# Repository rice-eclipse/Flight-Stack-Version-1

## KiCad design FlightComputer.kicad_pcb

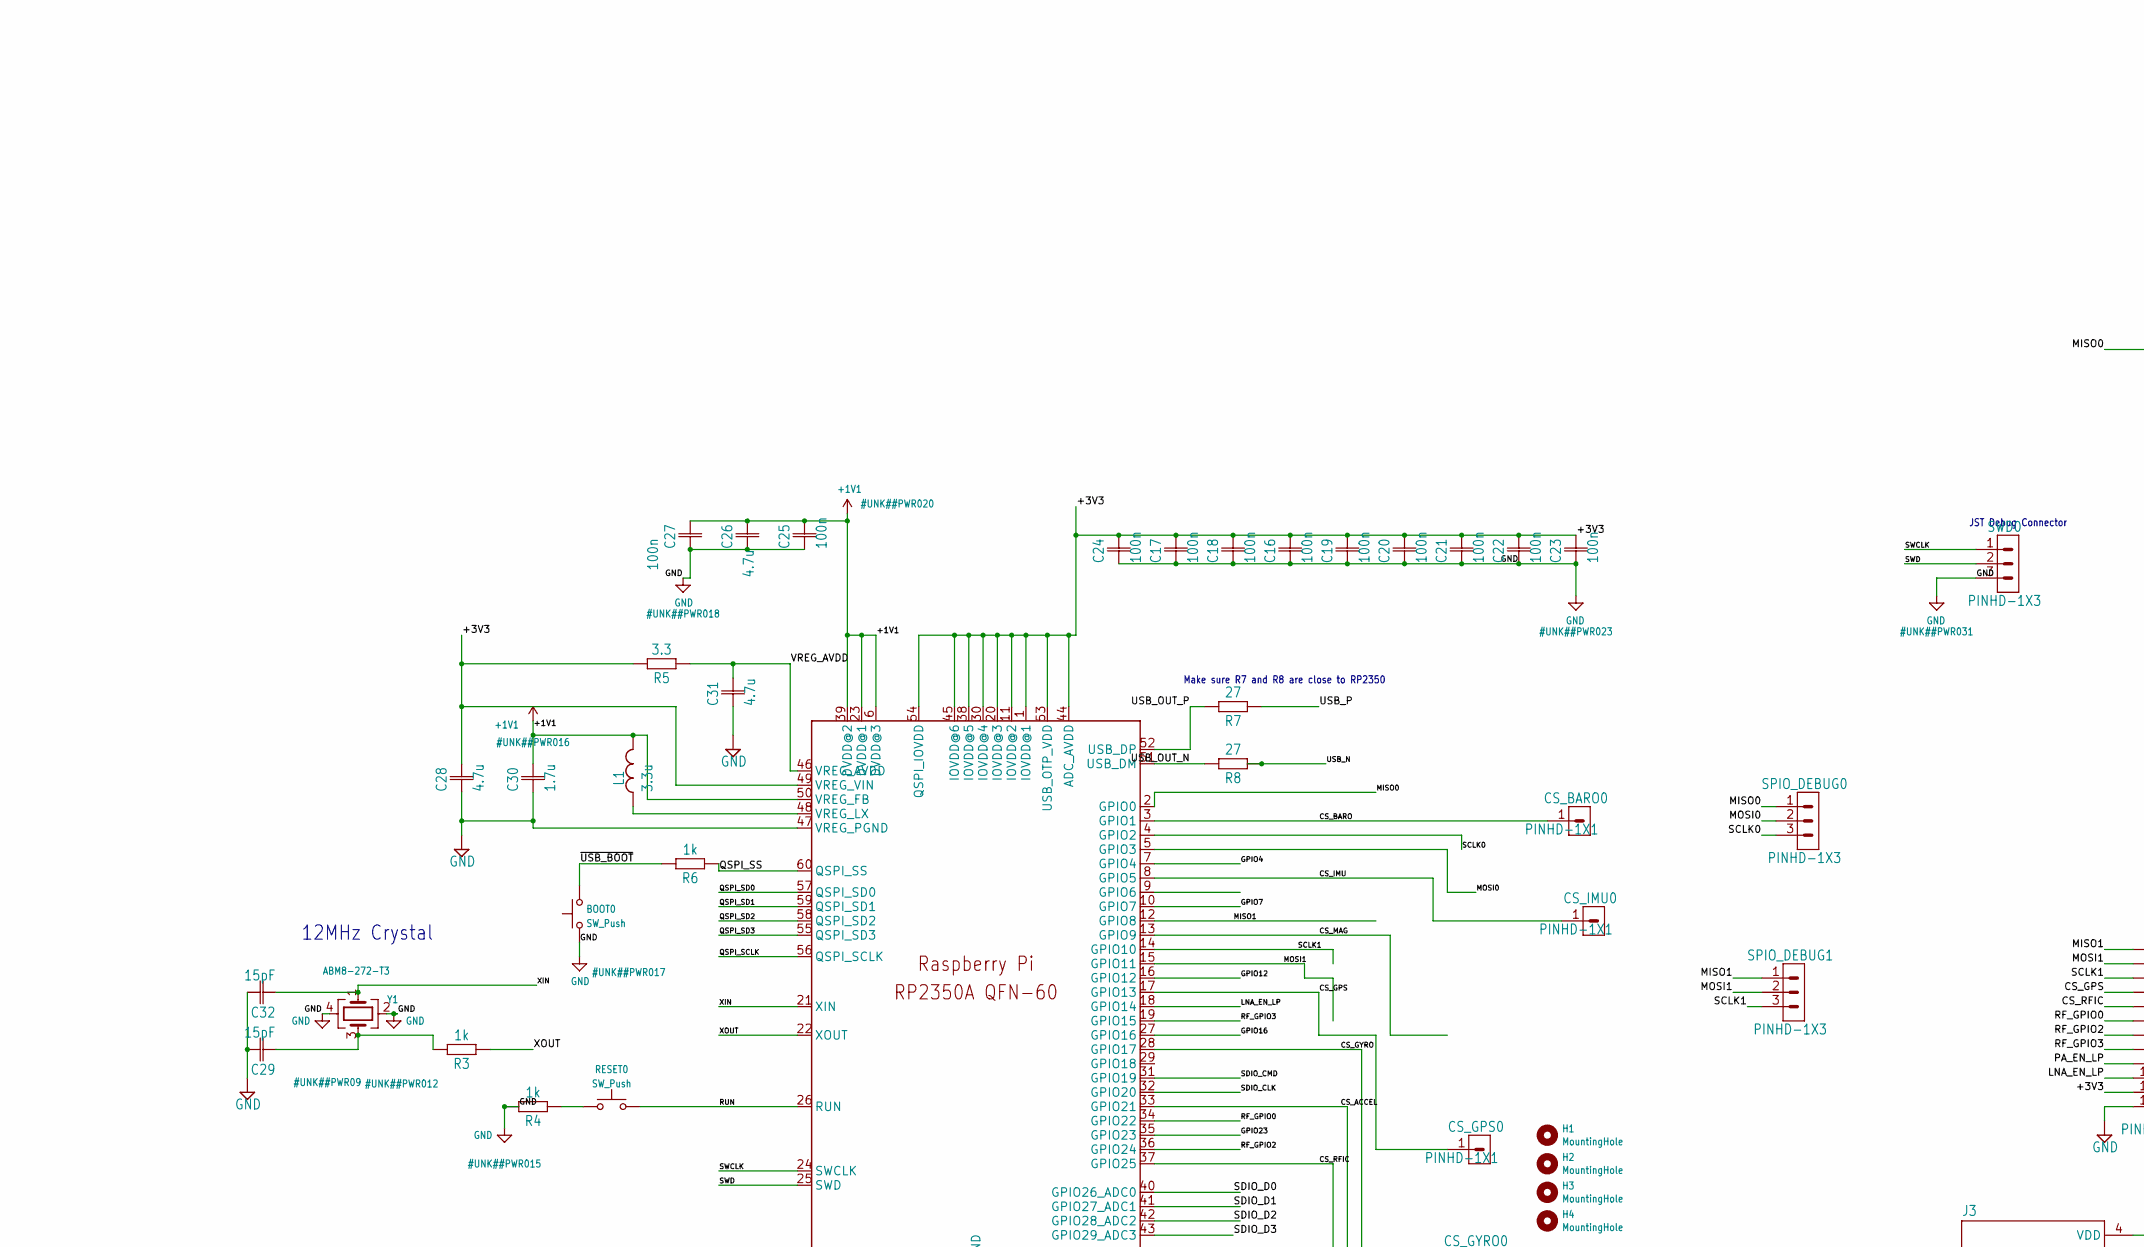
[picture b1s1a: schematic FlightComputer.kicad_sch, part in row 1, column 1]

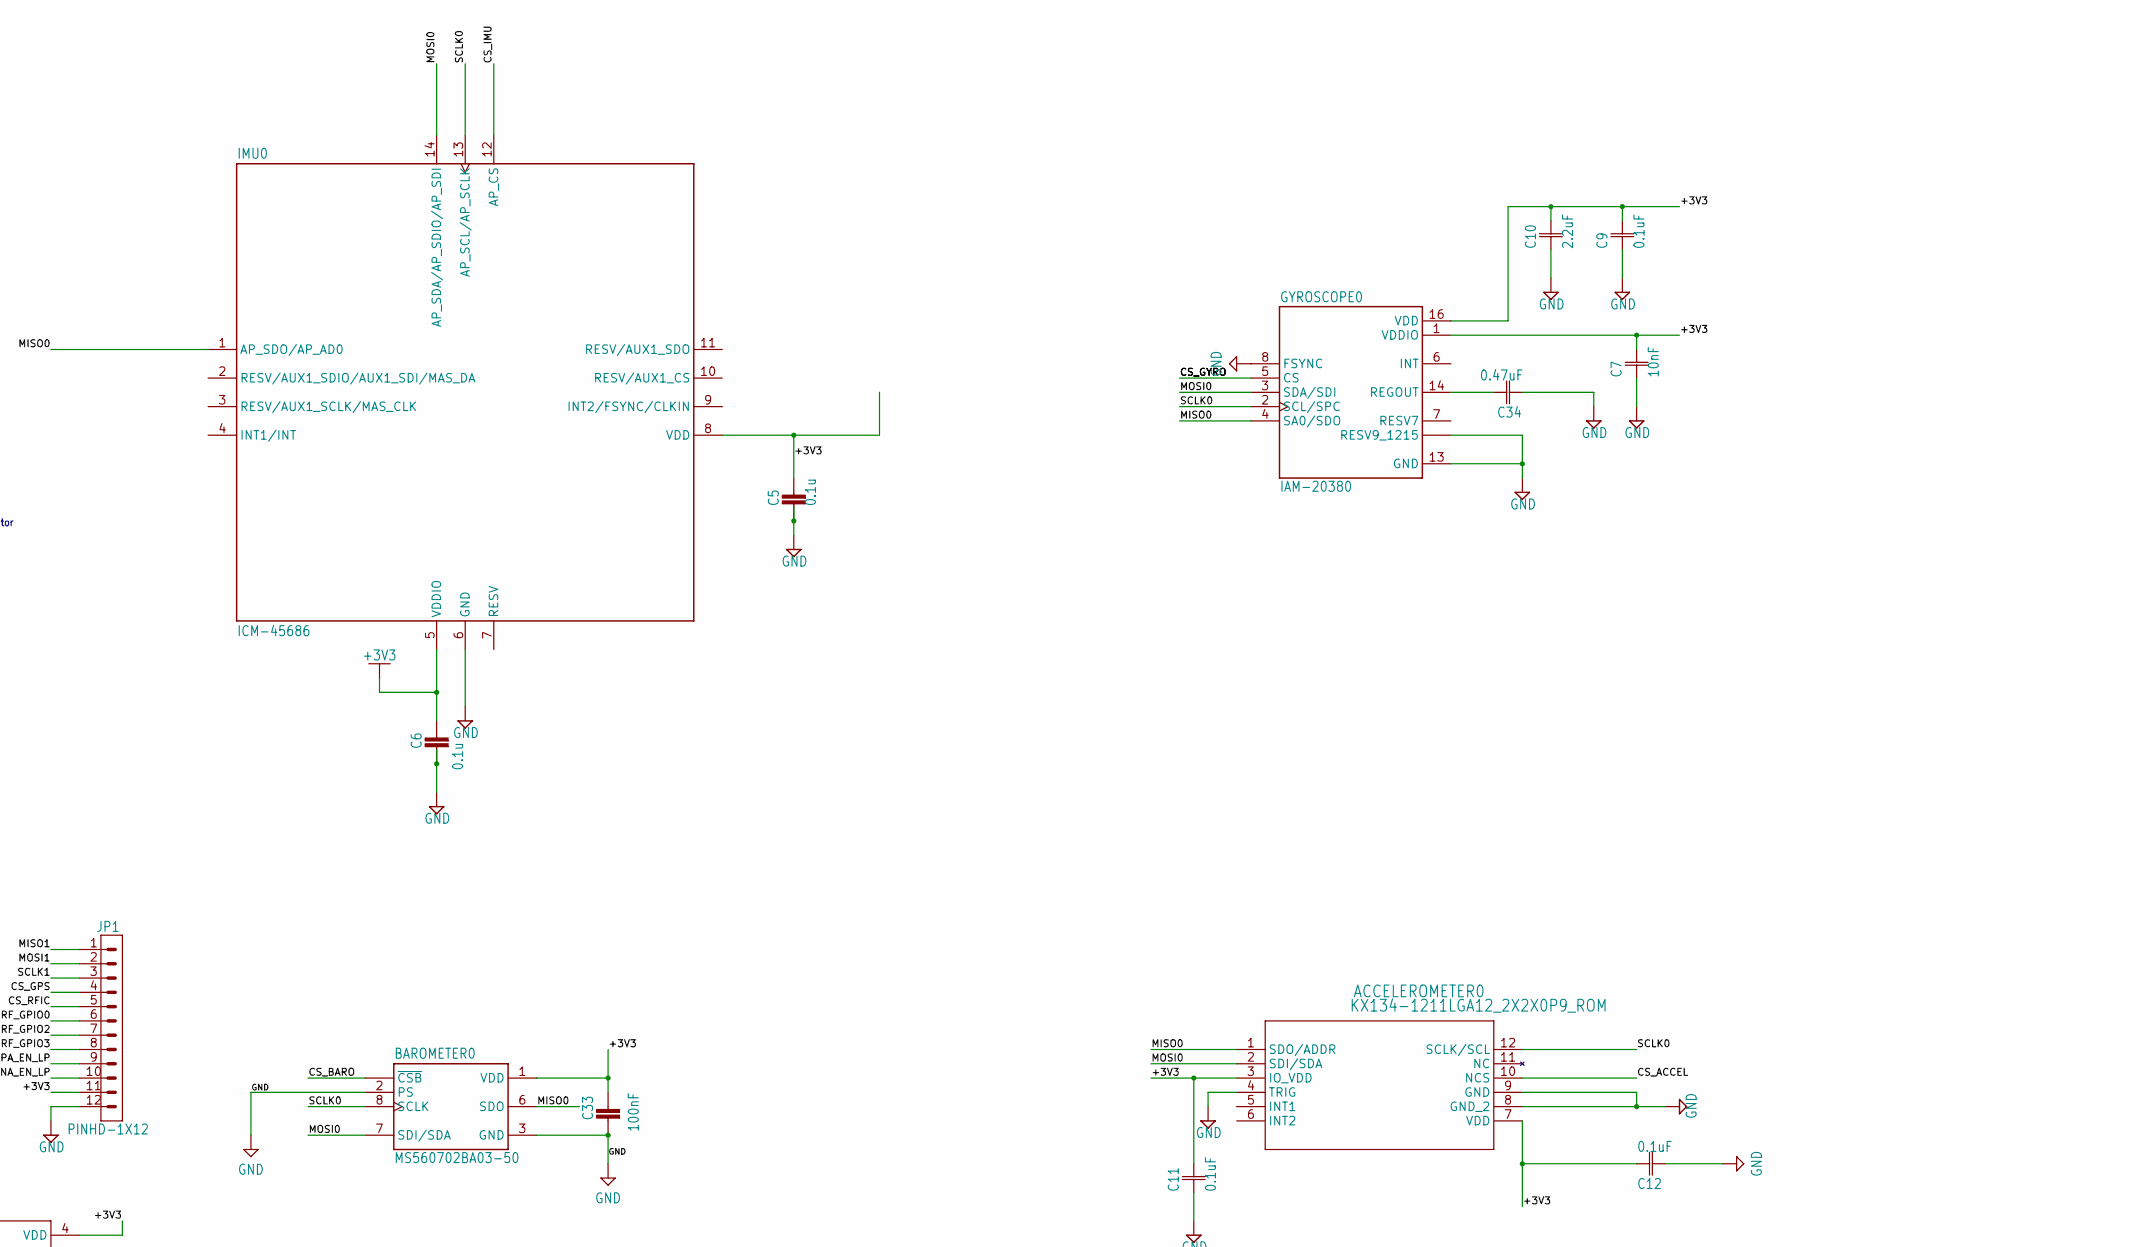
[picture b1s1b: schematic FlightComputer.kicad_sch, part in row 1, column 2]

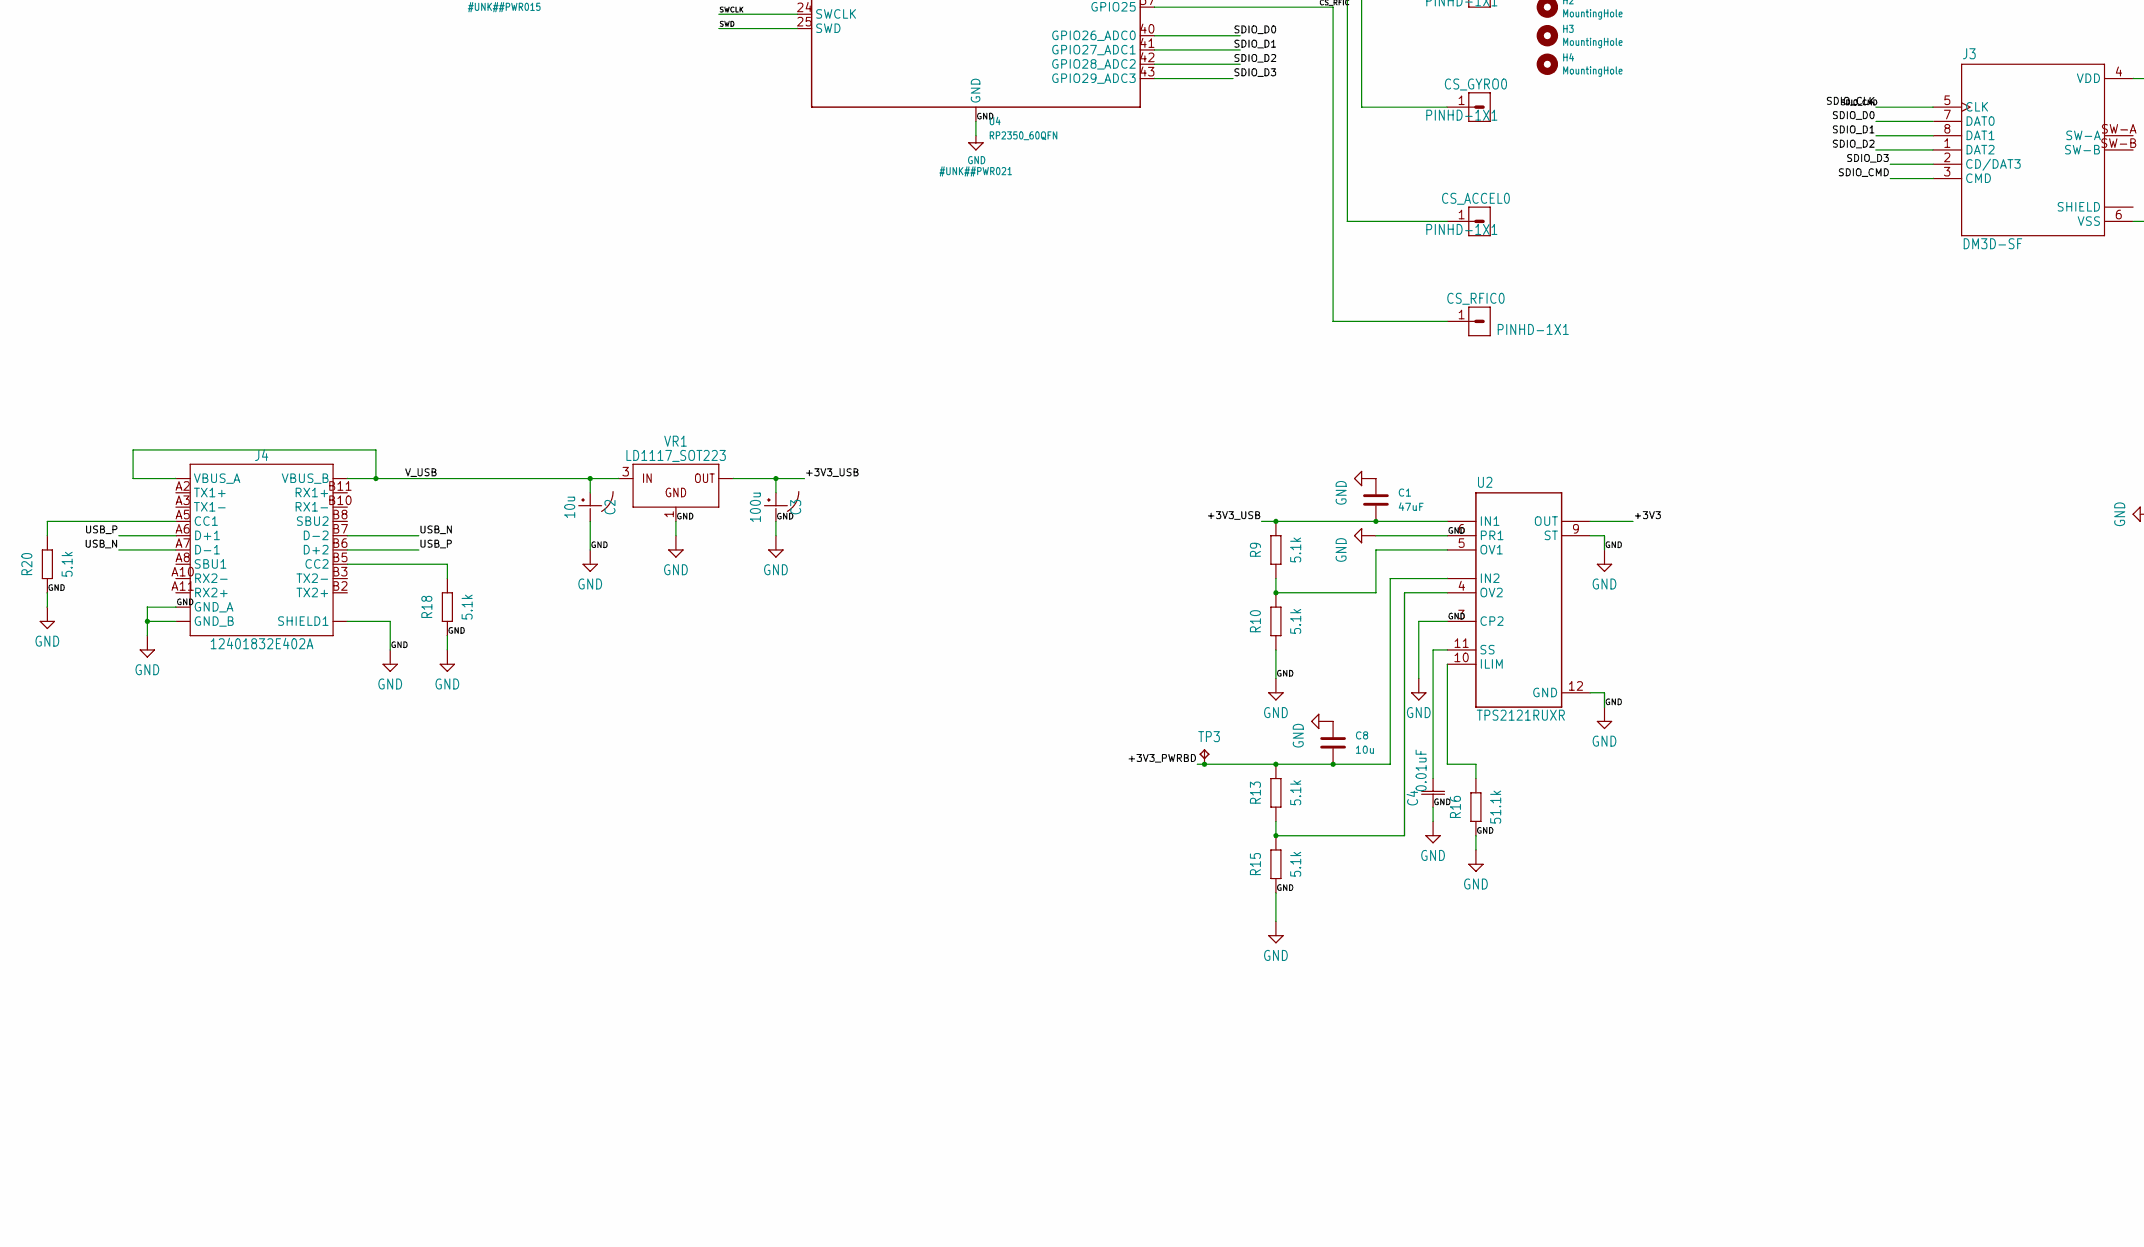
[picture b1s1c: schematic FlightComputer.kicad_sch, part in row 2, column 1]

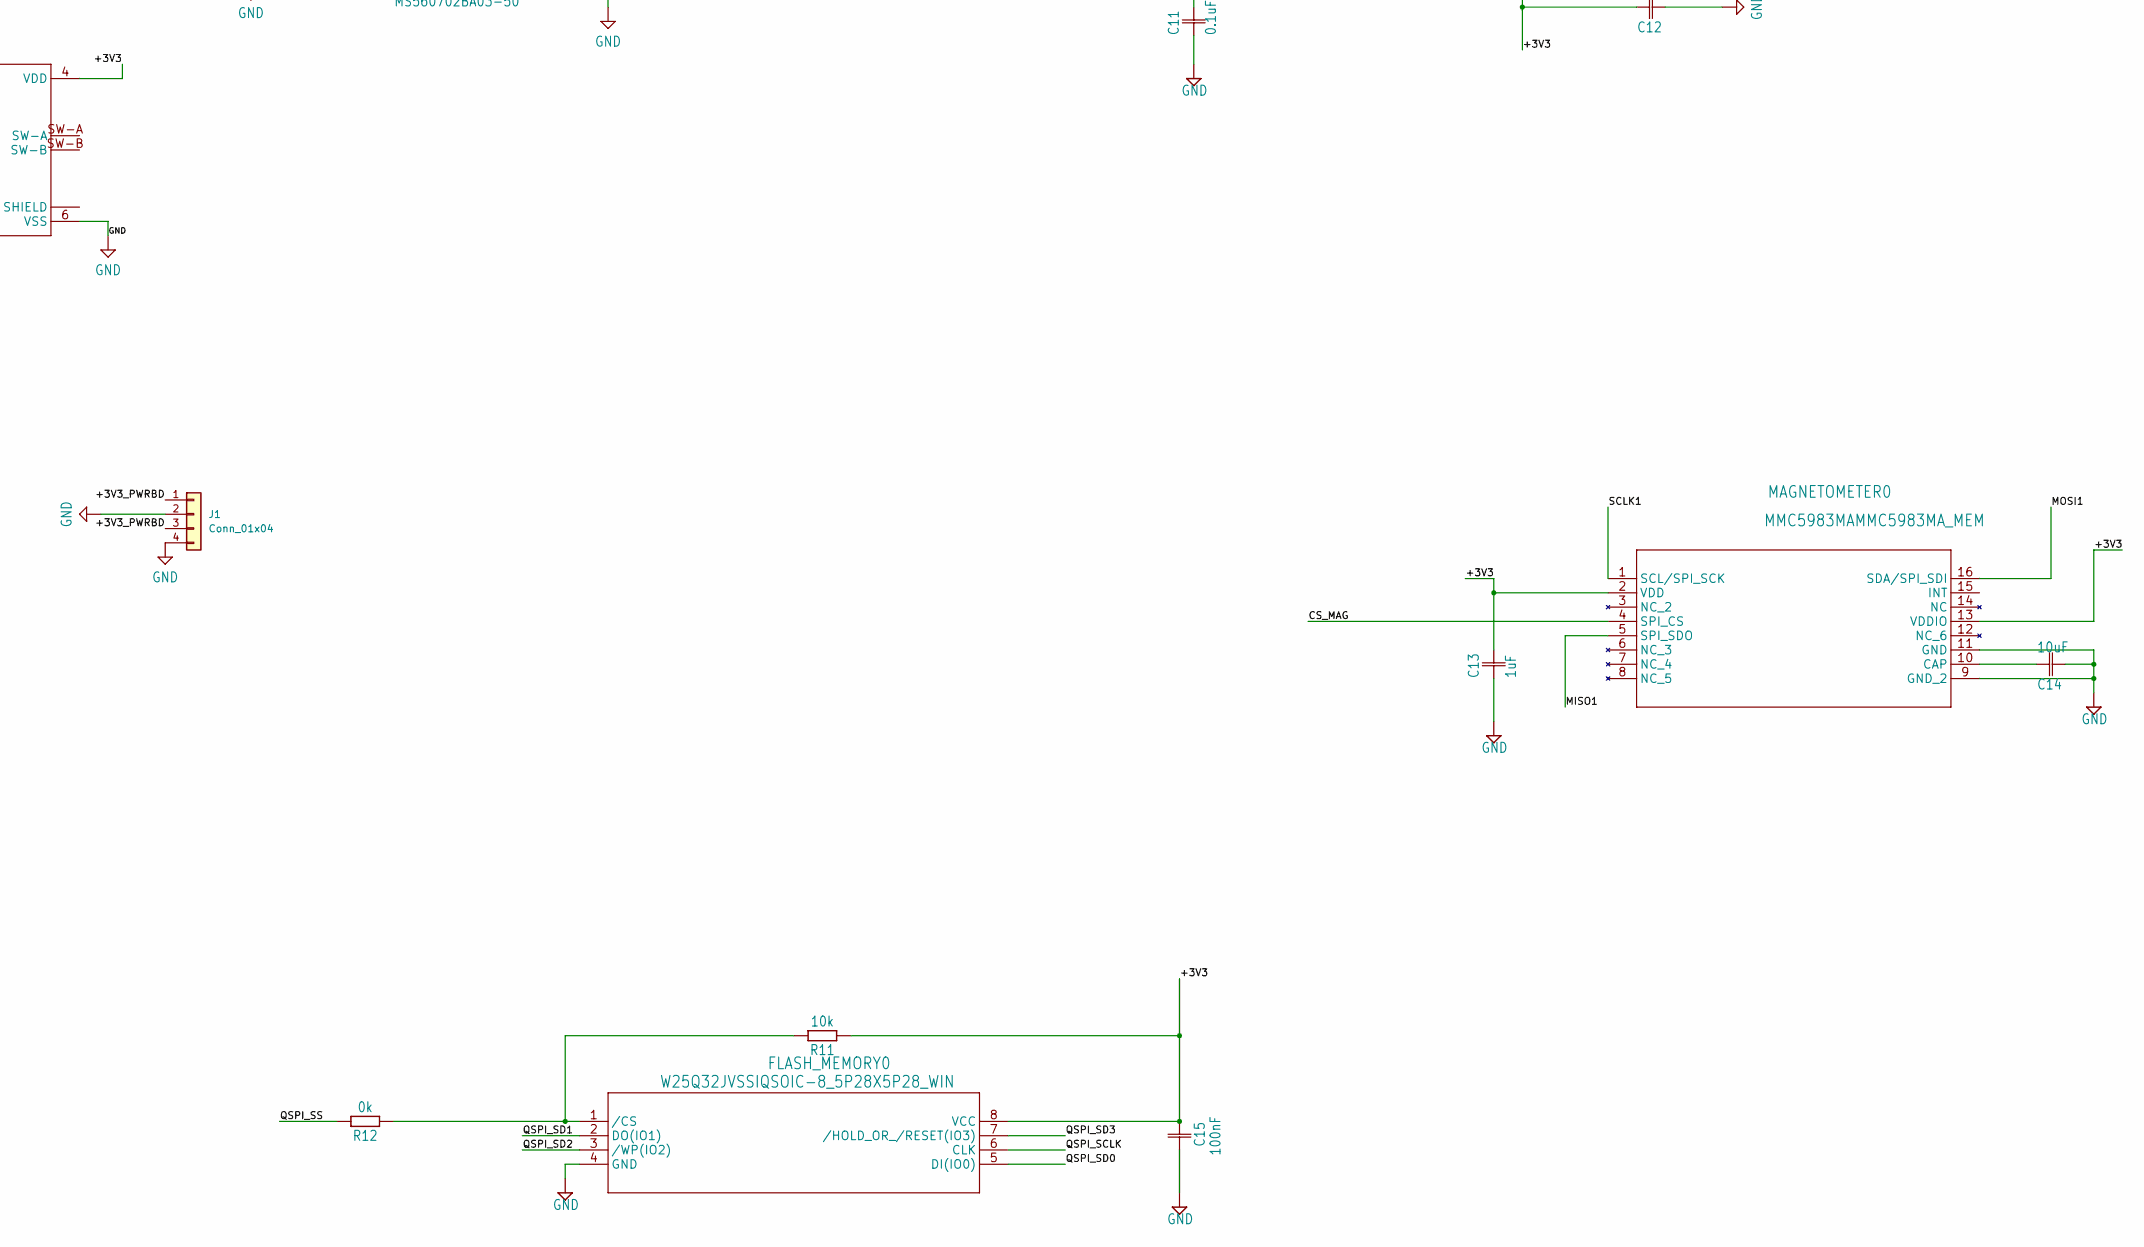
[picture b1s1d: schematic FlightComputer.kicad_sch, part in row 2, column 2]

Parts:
ACCELEROMETER0: KX134-1211LGA12_2X2X0P9_ROM; LGA12_2X2X0P9_ROM
BAROMETER0: MS560702BA03-50; SON125P300X500X100-8N
BOOT0: SW_Push; SW_Push_1P1T_NO_Vertical_Wuerth_434133025816
C1: 47uF
C2: 10u; CAPMP3216X180N
C3: 100u; CAPMP3216X180N
C4: 0.01uF; CAPC1005X60
C5, C6: 0.1u; CAPC2012X110
C7: 10nF; CAPC1608X85
C8: 10u
C9, C11, C12: 0.1uF; CAPC1608X85
C10: 2.2uF; CAPC1608X85
C13: 1uF; CAPC1608X85
C14: 10uF; CAPC1608X85
C15: 100nF; CAPC1608X85
C16, C17, C18, C20, C21, C22, C23, C24, C25, C27: 100n; CAPC1608X85
C19: 100n; CAPC1005X60
C26, C28, C31: 4.7u; CAPC1608X85
C29, C32: 15pF; CAPC1005X60
C30: 1.7u; CAPC1608X85
C33: 100nF; CAPC2012X110
C34: 0.47uF; CAPC1608X85
CS_ACCEL0: PINHD-1X1; 1X01
CS_BARO0: PINHD-1X1; 1X01
CS_GPS0: PINHD-1X1; 1X01
CS_GYRO0: PINHD-1X1; 1X01
CS_IMU0: PINHD-1X1; 1X01
CS_RFIC0: PINHD-1X1; 1X01
FLASH_MEMORY0: W25Q32JVSSIQSOIC-8_5P28X5P28_WIN; SOIC-8_5P28X5P28_WIN
GYROSCOPE0: IAM-20380; PQFN50P300X300X80-16N
H1, H2, H3, H4: MountingHole; MountingHole_2.7mm_M2.5
IMU0: ICM-45686; IC_ICM-45686
J1: Conn_01x04; JST_GH_BM04B-GHS-TBT_1x04-1MP_P1.25mm_Vertical
J3: DM3D-SF; HRS_DM3D-SF
J4: 12401832E402A
JP1: PINHD-1X12; 1X12
L1: 3.3u; INDC2009X120
MAGNETOMETER0: MMC5983MAMMC5983MA_MEM; MMC5983MA_MEM
R3: 1k; RESC1005X40
R4, R6: 1k; RESC1608X60
R5: 3.3; RESC1608X60
R7, R8: 27; RESC1608X60
R9, R10, R13, R15, R18, R20: 5.1k; RESC1005X40
R11: 10k; RESC2012X65
R12: 0k; RESC2012X65
R16: 51.1k; RESC1005X40
RESET0: SW_Push; SW_Push_1P1T_NO_Vertical_Wuerth_434133025816
SPIO_DEBUG0, SPIO_DEBUG1: PINHD-1X3; 1X03
SWD0: PINHD-1X3; 1X03
TP3: TPB1,27; B1,27
U2: TPS2121RUXR; IC_TPS2121RUXR
U4: RP2350_60QFN; RP2350-QFN-60-1EP_7x7_P0.4mm_EP3.4x3.4mm_ThermalVias
VR1: LD1117_SOT223; SOT230P700X170-4
Y1: ABM8-272-T3; Crystal_SMD_3225-4Pin_3.2x2.5mm

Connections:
+1V1: C25.2, C26.2, C27.2, C30.2, L1.2, U4.6 (DVDD@3), U4.23 (DVDD@1), U4.39 (DVDD@2), U4.50 (VREG_FB)
+3V3: ACCELEROMETER0.3 (IO_VDD), ACCELEROMETER0.7 (VDD), BAROMETER0.1 (VDD), C5.1, C6.1, C7.2, C9.2, C10.2, C11.2, C12.1, C13.2, C15.1, C16.2, C17.2, C18.2, C19.2, C20.2, C21.2, C22.2, C23.2, C24.2, C28.2, C33.1, FLASH_MEMORY0.8 (VCC), GYROSCOPE0.1 (VDDIO), GYROSCOPE0.16 (VDD), IMU0.5 (VDDIO), IMU0.8 (VDD), J3.4 (VDD), JP1.11, MAGNETOMETER0.2 (VDD), MAGNETOMETER0.13 (VDDIO), R5.2, R11.1, U2.1 (OUT), U2.1_1 (OUT), U2.8 (OUT), U2.8_1 (OUT), U4.1 (IOVDD@1), U4.11 (IOVDD@2), U4.20 (IOVDD@3), U4.30 (IOVDD@4), U4.38 (IOVDD@5), U4.44 (ADC_AVDD), U4.45 (IOVDD@6), U4.49 (VREG_VIN), U4.53 (USB_OTP_VDD), U4.54 (QSPI_IOVDD)
/+3V3_PWRBD: C8.2, J1.1, J1.3, R13.2, TP3.TP (TP_TP), U2.2 (IN2), U2.2_1 (IN2)
/+3V3_USB: C1.2, C3.1 (+), R9.2, U2.7 (IN1), U2.7_1 (IN1), VR1.2 (VO), VR1.4 (VO)
/CS_ACCEL: ACCELEROMETER0.10 (NCS), CS_ACCEL0.1 (1_1), U4.33 (GPIO21)
/CS_BARO: BAROMETER0.4 (~CSB), BAROMETER0.5 (~CSB), CS_BARO0.1 (1_1), U4.3 (GPIO1)
/CS_GPS: CS_GPS0.1 (1_1), JP1.4, U4.17 (GPIO13)
/CS_GYRO: CS_GYRO0.1 (1_1), GYROSCOPE0.5 (CS), U4.28 (GPIO17)
/CS_IMU: CS_IMU0.1 (1_1), IMU0.12 (AP_CS), U4.8 (GPIO5)
/CS_MAG: MAGNETOMETER0.4 (SPI_CS), U4.13 (GPIO9)
/CS_RFIC: CS_RFIC0.1 (1_1), JP1.5, U4.37 (GPIO25)
/GPIO4: U4.7 (GPIO4)
/GPIO7: U4.10 (GPIO7)
/GPIO12: U4.16 (GPIO12)
/GPIO16: U4.27 (GPIO16)
/GPIO23: U4.35 (GPIO23)
/LNA_EN_LP: JP1.10, U4.18 (GPIO14)
/MISO0: ACCELEROMETER0.1 (SDO/ADDR), BAROMETER0.6 (SDO), GYROSCOPE0.4 (SA0/SDO), IMU0.1 (AP_SDO/AP_AD0), SPIO_DEBUG0.1, U4.2 (GPIO0)
/MISO1: JP1.1, MAGNETOMETER0.5 (SPI_SDO), SPIO_DEBUG1.1, U4.12 (GPIO8)
/MOSI0: ACCELEROMETER0.2 (SDI/SDA), BAROMETER0.7 (SDI/SDA), GYROSCOPE0.3 (SDA/SDI), IMU0.14 (AP_SDA/AP_SDIO/AP_SDI), SPIO_DEBUG0.2, U4.5 (GPIO3)
/MOSI1: JP1.2, MAGNETOMETER0.16 (SDA/SPI_SDI), SPIO_DEBUG1.2, U4.15 (GPIO11)
/PA_EN_LP: JP1.9
/QSPI_SCLK: FLASH_MEMORY0.6 (CLK), U4.56 (QSPI_SCLK)
/QSPI_SD0: FLASH_MEMORY0.5 (DI(IO0)), U4.57 (QSPI_SD0)
/QSPI_SD1: FLASH_MEMORY0.2 (DO(IO1)), U4.59 (QSPI_SD1)
/QSPI_SD2: FLASH_MEMORY0.3 (/WP(IO2)), U4.58 (QSPI_SD2)
/QSPI_SD3: FLASH_MEMORY0.7 (/HOLD_OR_/RESET(IO3)), U4.55 (QSPI_SD3)
/QSPI_SS: R6.1, R12.2, U4.60 (QSPI_SS)
/RF_GPIO0: JP1.6, U4.34 (GPIO22)
/RF_GPIO2: JP1.7, U4.36 (GPIO24)
/RF_GPIO3: JP1.8, U4.19 (GPIO15)
/RUN: RESET0.2_1 (2), RESET0.2_2 (2), U4.26 (RUN)
/SCLK0: ACCELEROMETER0.12 (SCLK/SCL), BAROMETER0.8 (SCLK), GYROSCOPE0.2 (SCL/SPC), IMU0.13 (AP_SCL/AP_SCLK), SPIO_DEBUG0.3, U4.4 (GPIO2)
/SCLK1: JP1.3, MAGNETOMETER0.1 (SCL/SPI_SCK), SPIO_DEBUG1.3, U4.14 (GPIO10)
/SDIO_CLK: J3.5 (CLK), U4.32 (GPIO20)
/SDIO_CMD: J3.3 (CMD), U4.31 (GPIO19)
/SDIO_D0: J3.7 (DAT0), U4.40 (GPIO26_ADC0)
/SDIO_D1: J3.8 (DAT1), U4.41 (GPIO27_ADC1)
/SDIO_D2: J3.1 (DAT2), U4.42 (GPIO28_ADC2)
/SDIO_D3: J3.2 (CD/DAT3), U4.43 (GPIO29_ADC3)
/SWCLK: SWD0.1, U4.24 (SWCLK)
/SWD: SWD0.2, U4.25 (SWD)
/USB_N: J4.A7 (D-1), J4.B7 (D-2), R8.1
/USB_OUT_N: R8.2, U4.51 (USB_DM)
/USB_OUT_P: R7.2, U4.52 (USB_DP)
/USB_P: J4.A6 (D+1), J4.B6 (D+2), R7.1
/VREG_AVDD: C31.2, R5.1, U4.46 (VREG_AVDD)
/V_USB: C2.1 (+), J4.A4 (VBUS_A), J4.A9 (VBUS_A), J4.B4 (VBUS_B), J4.B9 (VBUS_B), VR1.3 (VI)
/XIN: C32.1, U4.21 (XIN), Y1.1
/XOUT: R3.1, U4.22 (XOUT)
/~USB_BOOT: BOOT0.2_1 (2), BOOT0.2_2 (2), R6.2
GND: ACCELEROMETER0.4 (TRIG), ACCELEROMETER0.8 (GND_2), ACCELEROMETER0.9 (GND), BAROMETER0.2 (PS), BAROMETER0.3 (GND), BOOT0.1_1 (1), BOOT0.1_2 (1), C1.1, C2.2 (-), C3.2 (-), C4.1, C5.2, C6.2, C7.1, C8.1, C9.1, C10.1, C11.1, C12.2, C13.1, C14.2, C15.2, C16.1, C17.1, C18.1, C19.1, C20.1, C21.1, C22.1, C23.1, C24.1, C25.1, C26.1, C27.1, C28.1, C29.2, C30.1, C31.1, C32.2, C33.2, C34.1, FLASH_MEMORY0.4 (GND), GYROSCOPE0.8 (FSYNC), GYROSCOPE0.9 (RESV9_1215), GYROSCOPE0.10 (RESV9_1215), GYROSCOPE0.11 (RESV9_1215), GYROSCOPE0.12 (RESV9_1215), GYROSCOPE0.13 (GND), GYROSCOPE0.15 (RESV9_1215), IMU0.6 (GND), J1.2, J1.4, J3.6 (VSS), J4.A1 (GND_A), J4.A12 (GND_A), J4.B1 (GND_B), J4.B12 (GND_B), J4.SH1 (SHIELD1), J4.SH2 (SHIELD1), J4.SH3 (SHIELD1), J4.SH4 (SHIELD1), JP1.12, MAGNETOMETER0.9 (GND_2), MAGNETOMETER0.11 (GND), R4.2, R10.1, R15.1, R16.1, R18.1, R20.1, SWD0.3, U2.3 (CP2), U2.6 (PR1), U2.9 (ST), U2.12 (GND), U4.47 (VREG_PGND), U4.61_1 (GND), U4.61_2 (GND), U4.61_3 (GND), U4.61_4 (GND), U4.61_5 (GND), U4.61_6 (GND), U4.61_7 (GND), U4.61_8 (GND), U4.61_9 (GND), U4.61_10 (GND), VR1.1 (GND), Y1.2, Y1.4
unnamed: C29.1, R3.2, Y1.3
unnamed: FLASH_MEMORY0.1 (/CS), R11.2, R12.1
unnamed: C34.2, GYROSCOPE0.14 (REGOUT)
unnamed: J3.S1 (SHIELD), J3.S2 (SHIELD), J3.S3 (SHIELD), J3.S4 (SHIELD)
unnamed: J4.A5 (CC1), R20.2
unnamed: J4.B5 (CC2), R18.2
unnamed: C14.1, MAGNETOMETER0.10 (CAP)
unnamed: R4.1, RESET0.1_1 (1), RESET0.1_2 (1)
unnamed: R16.2, U2.10 (ILIM)
unnamed: R9.1, R10.2, U2.5 (OV1)
unnamed: R13.1, R15.2, U2.4 (OV2)
unnamed: C4.2, U2.11 (SS)
unnamed: L1.1, U4.48 (VREG_LX)

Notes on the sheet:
JST Debug Connector
12MHz Crystal
Make sure R7 and R8 are close to RP2350

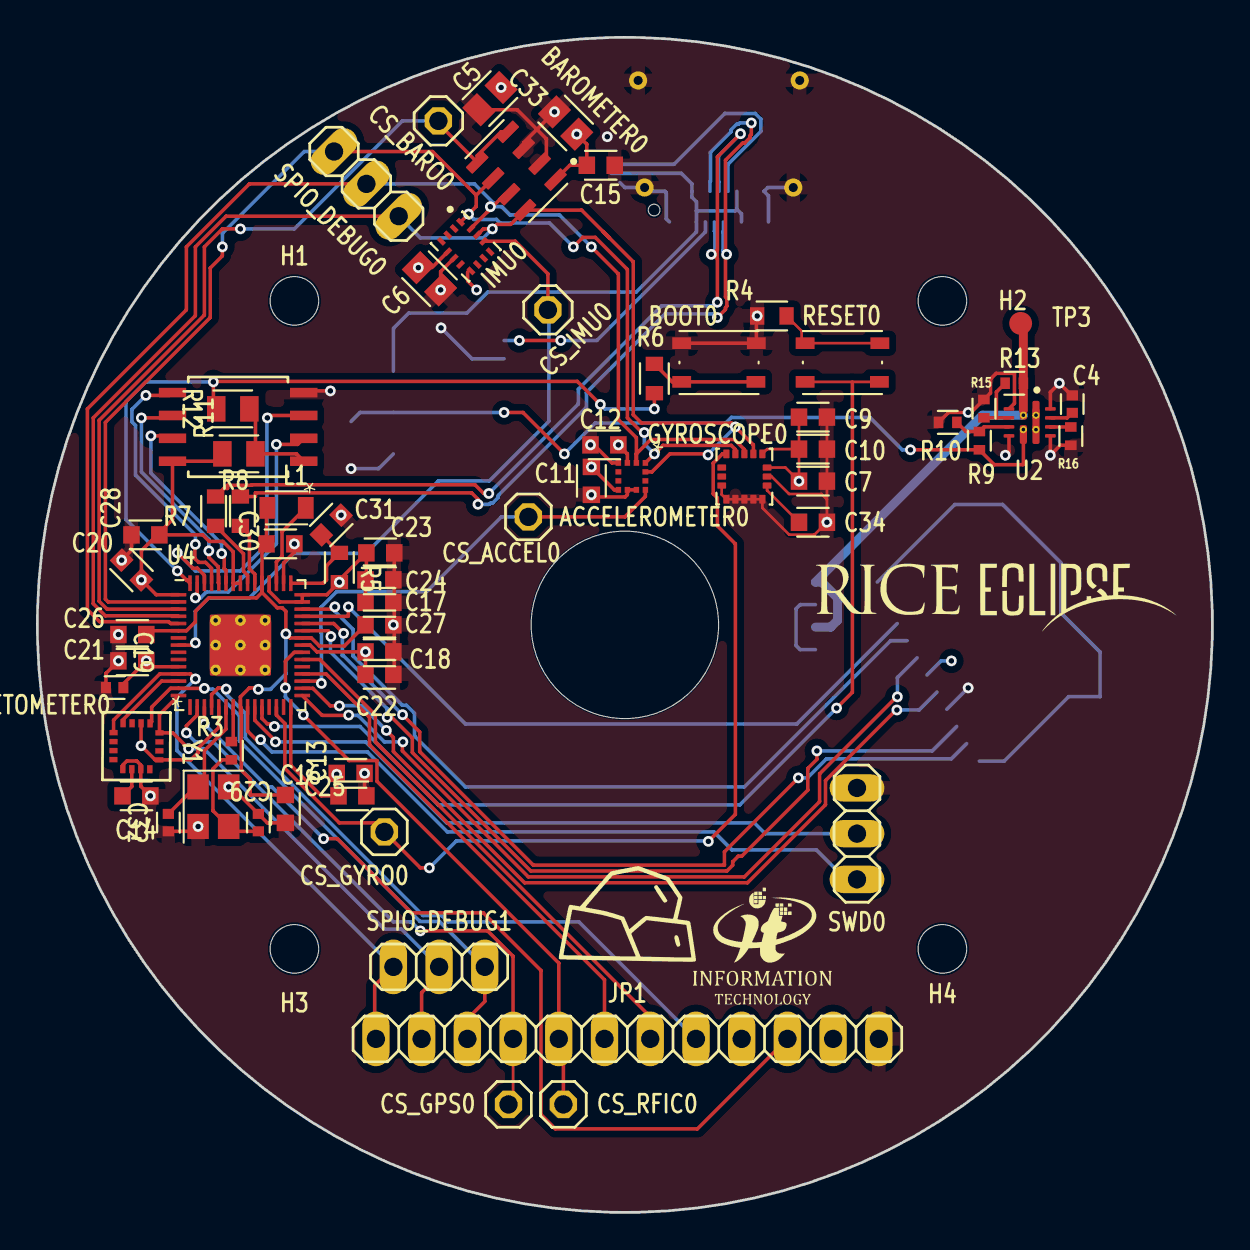
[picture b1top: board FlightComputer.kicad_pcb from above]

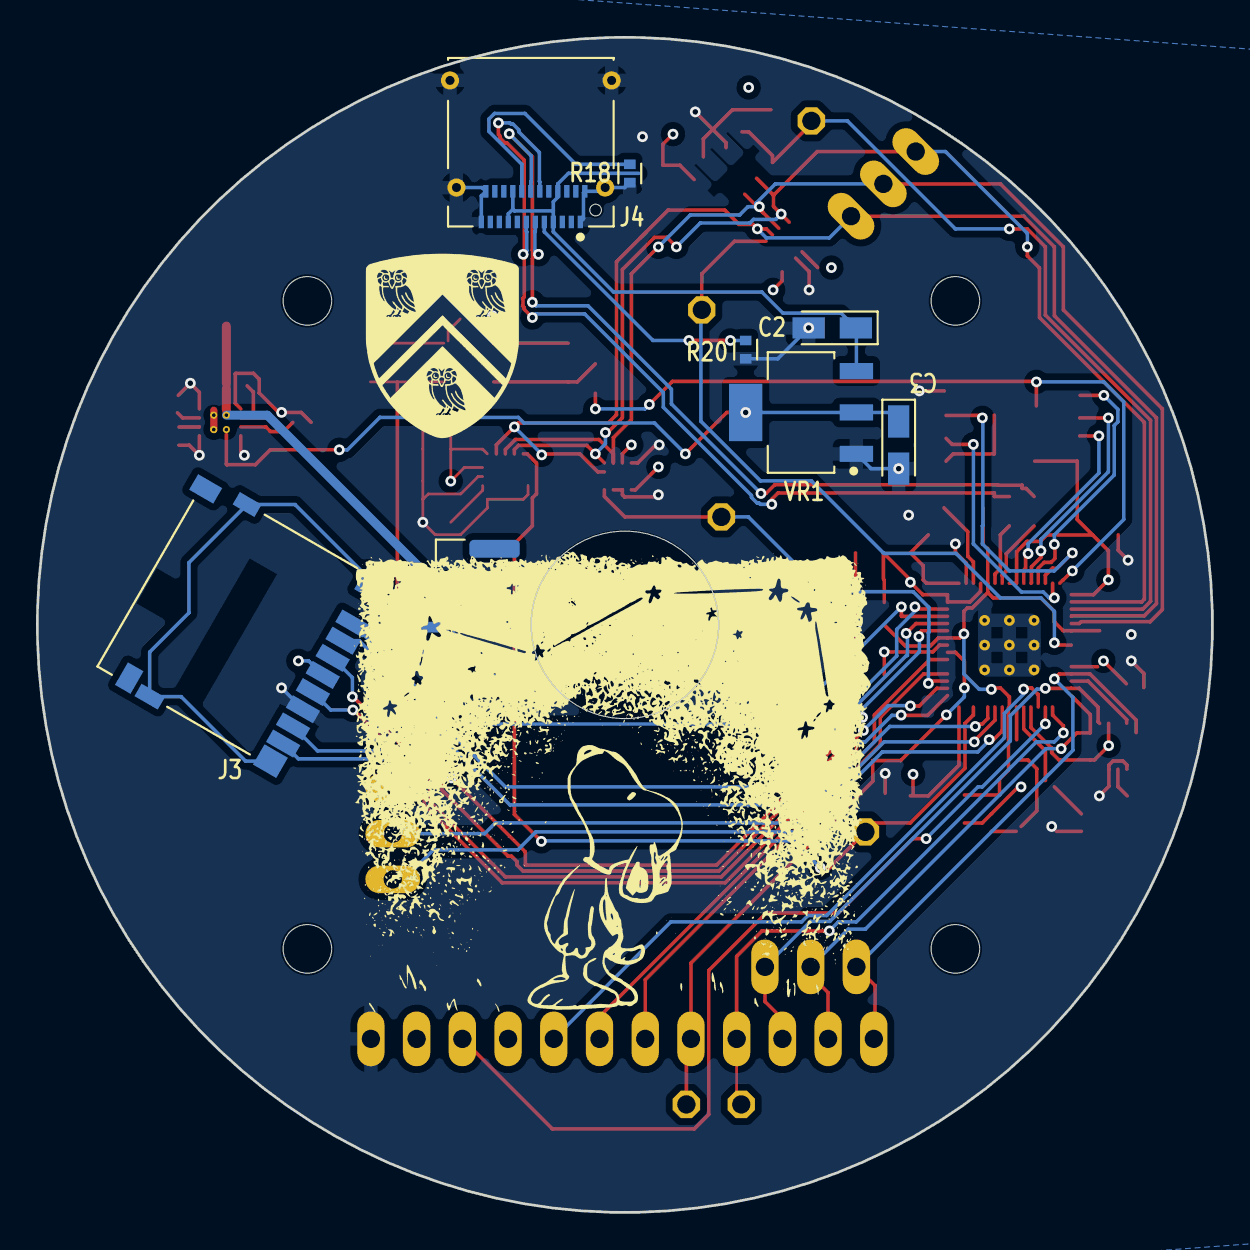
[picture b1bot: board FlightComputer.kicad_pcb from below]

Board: 4 copper layers, 65.3 x 65.3 mm, 78 parts (8 on the bottom side), 59 nets.
